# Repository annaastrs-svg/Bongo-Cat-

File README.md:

- BONGO CAT
  --

SEE BONGO CAT PAGE ! 
https://annaastrs-svg.github.io/bongo-pag/

A little cat that like playing bongos jeje 
is a esp32 with an oled 0.91 and 2 push buttons that when u press them it makes the cat play the bongos
and making a song with the buzzer.

https://github.com/user-attachments/assets/fc77c64f-0bb9-4f46-ad72-4055418aac2a

TRY ITTT !! 

SIMULATION IN WOKWI i ! :B
-----------------------------
https://wokwi.com/projects/465673627824576513

the btns are in the sides btw 

!! ESCHEMATIC  !!
--

!! PCB !!
--

 !! 3D !!
 --

!! BOM !!
--

!! WIRING TABLE  !!

ESP32 - OLED
--------------
GND - GND 
3V3 - VCC
21 - SDA 
22 - SCK

ESP32 - BTN 1 
----------------
GND - GND 
D 18 - S 

ESP32 - BTN 2
-------------
GND - GND
D 19 - S

!! CAD !!
--

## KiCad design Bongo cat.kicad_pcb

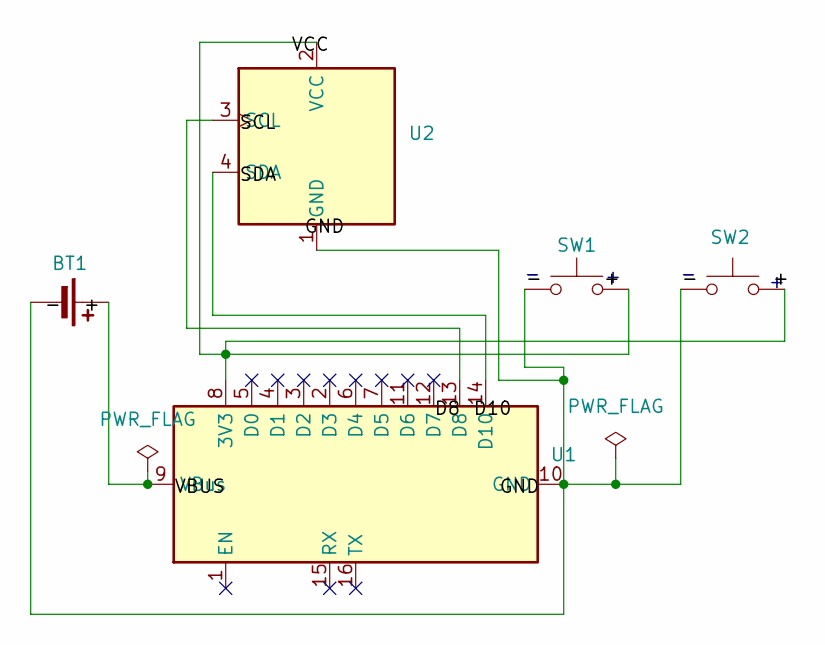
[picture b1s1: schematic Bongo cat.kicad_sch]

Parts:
BT1: Battery_Cell; PinHeader_1x02_P2.54mm_Vertical
SW1, SW2: SW_Push; SW_PUSH_6mm
U1: WEMOS_C3_mini; PinHeader_2x08_P2.54mm_Vertical
U2: ER_OLEDM0.91_1x-I2C; PinHeader_1x04_P2.54mm_Vertical

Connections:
/-: BT1.2 (-), SW1.1, SW2.1, U1.10 (GND), U2.1 (GND)
unnamed: BT1.1 (+), U1.9 (VBus)
unnamed: SW1.2, SW2.2, U1.8 (3V3), U2.2 (VCC)
unnamed: U1.13 (D8), U2.3 (SCL)
unnamed: U1.14 (D10), U2.4 (SDA)

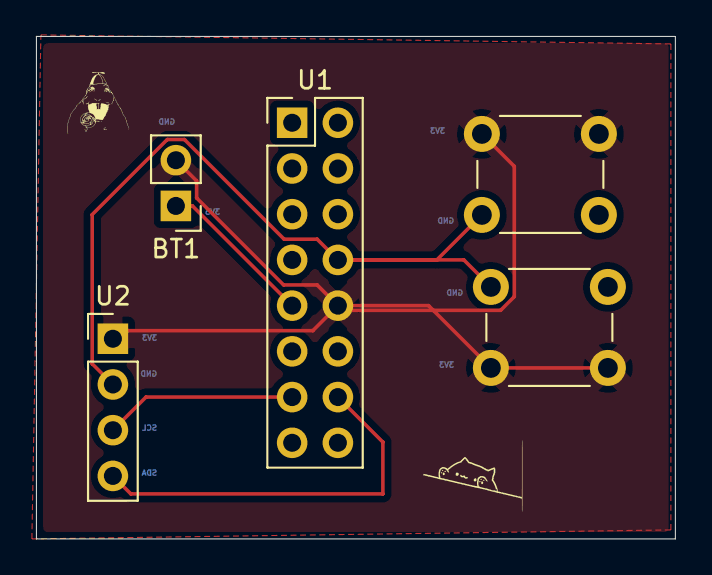
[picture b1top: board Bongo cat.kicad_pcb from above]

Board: 2 copper layers, 35.5 x 27.9 mm, 5 parts (0 on the bottom side), 5 nets.

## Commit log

2026-05-30 KiCad PCB DESIGN
2026-06-01 BONGO CAT CODE.ino
2026-06-02 CAD files
2026-06-03 PCB DESIGN
2026-06-11 Update README with new asset link
    Removed old image link and added a new one.
2026-06-18 Fix formatting and add separators in README.md
2026-06-18 Bongo BOM . csv
2026-06-18 Update README with new image and BOM section
    Added a new image to the README and updated the BOM section.
2026-06-19 BOM . CSV
